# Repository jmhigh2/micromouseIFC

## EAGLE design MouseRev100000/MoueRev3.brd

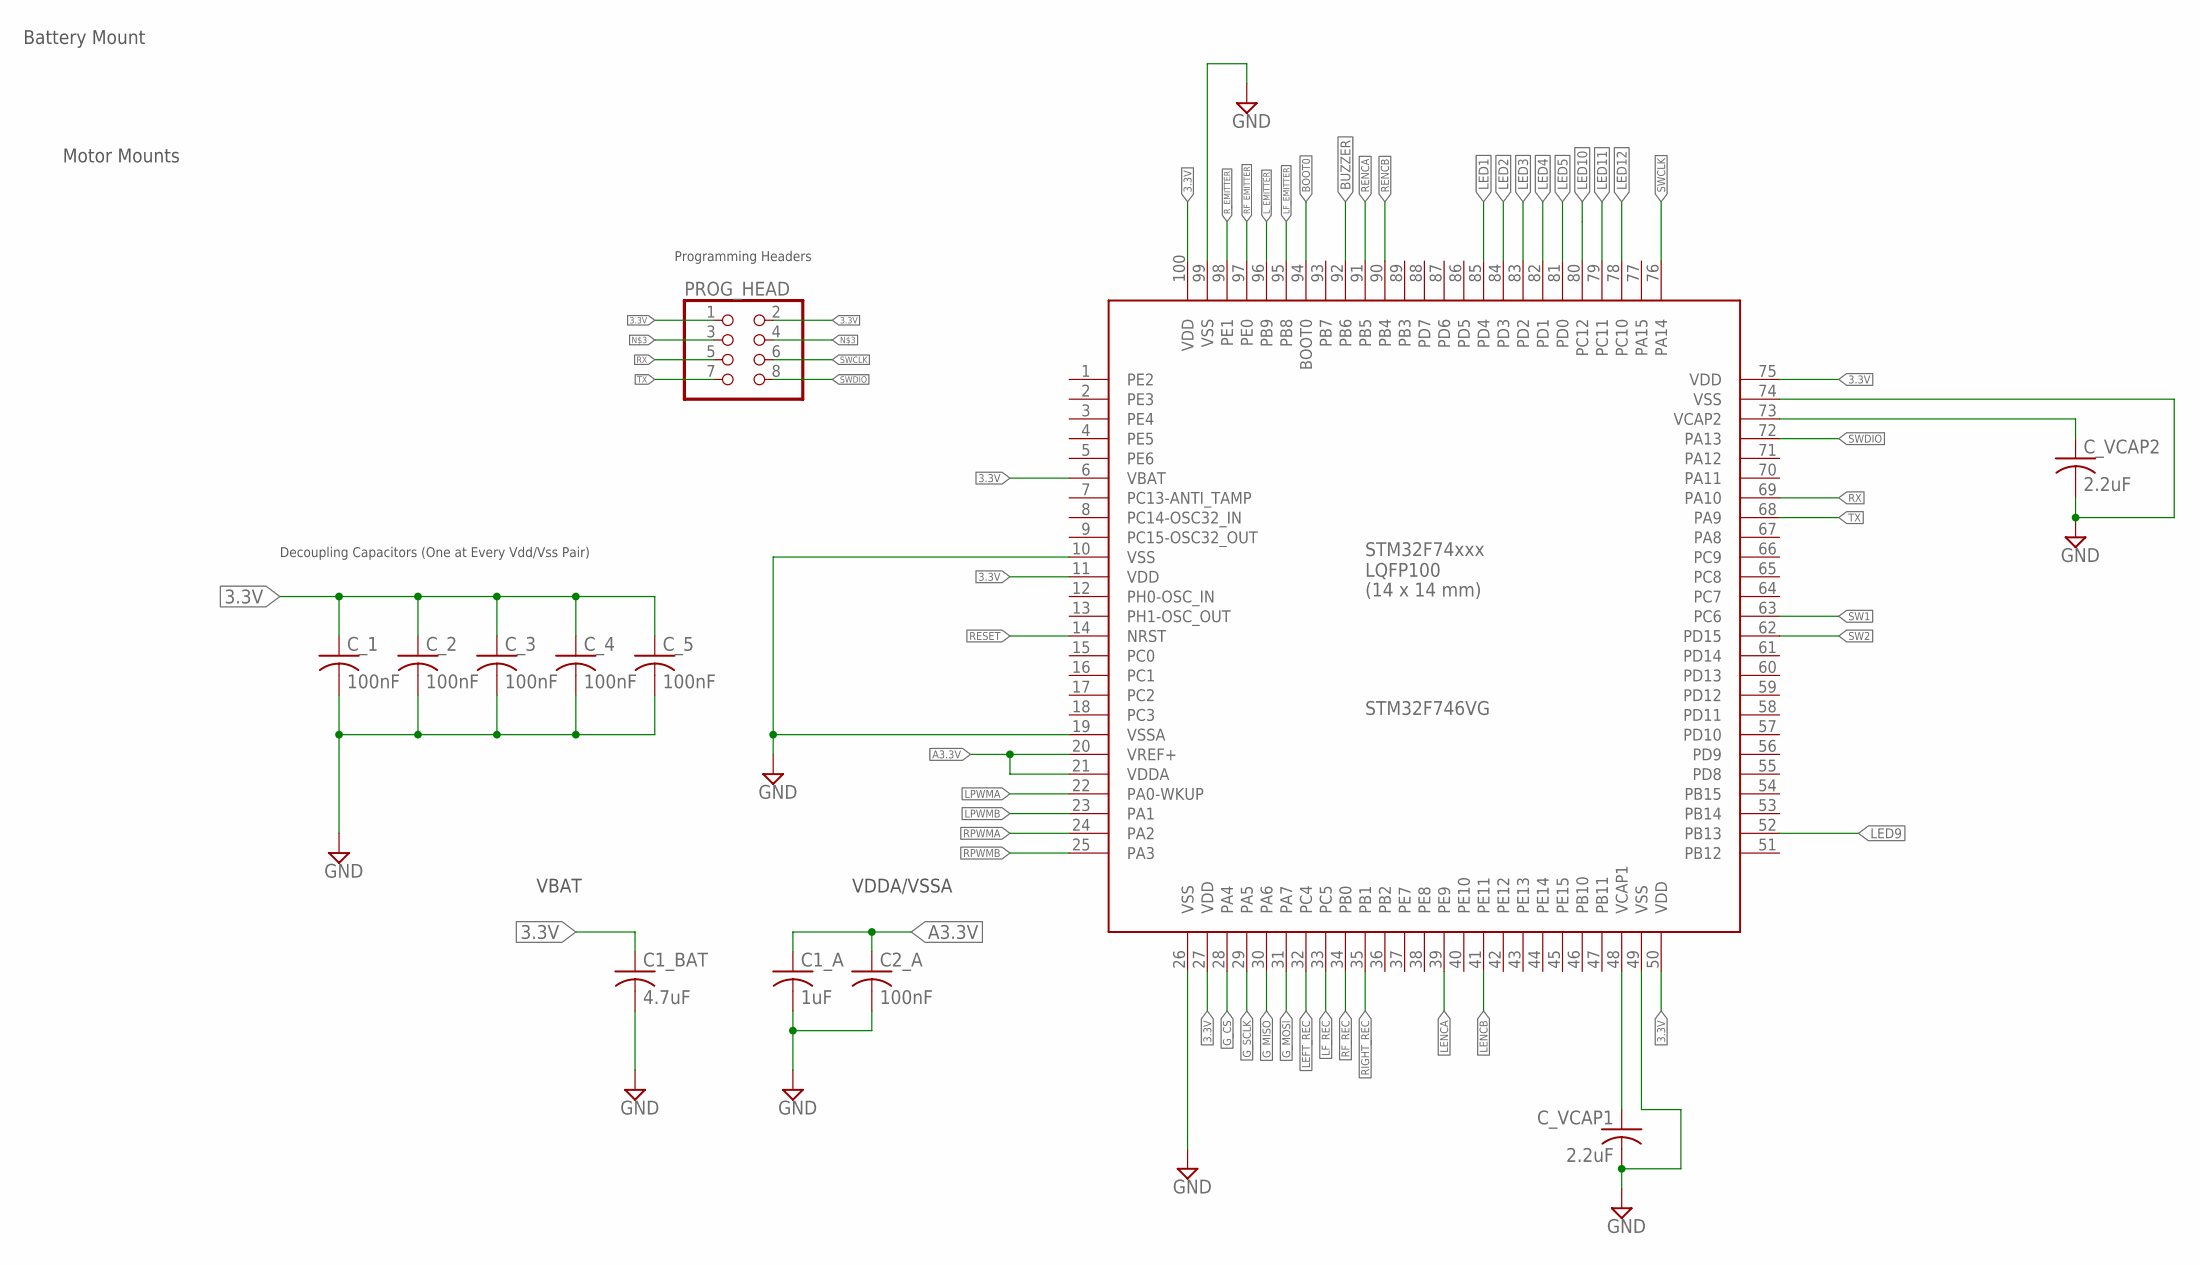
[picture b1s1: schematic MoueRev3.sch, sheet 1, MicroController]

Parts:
C1_A: 1uF; C0603
C1_BAT: 4.7uF; C0603
C2_A: 100nF; C0603
C_1, C_2, C_3, C_4, C_5: 100nF; C0603
C_VCAP1, C_VCAP2: 2.2uF; C0603
PROG_HEAD: PINHD-2X4; 2X04
U$2: MOTOR; MOTOR_MOUNT
U$3: STM32F746VG; LQFP100

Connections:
3.3V: C1_BAT.1, C_1.1, C_2.1, C_3.1, C_4.1, C_5.1, PROG_HEAD.1, PROG_HEAD.2, U$3.6 (VBAT), U$3.11 (VDD), U$3.27 (VDD), U$3.50 (VDD), U$3.75 (VDD), U$3.100 (VDD); also elsewhere on the board
A3.3V: C1_A.1, C2_A.1, U$3.20 (VREF+), U$3.21 (VDDA); also elsewhere on the board
BOOT0: U$3.94 (BOOT0); also elsewhere on the board
BUZZER: U$3.92 (PB6); also elsewhere on the board
G_CS: U$3.28 (PA4); also elsewhere on the board
G_MISO: U$3.30 (PA6); also elsewhere on the board
G_MOSI: U$3.31 (PA7); also elsewhere on the board
G_SCLK: U$3.29 (PA5); also elsewhere on the board
LED1: U$3.85 (PD4); also elsewhere on the board
LED2: U$3.84 (PD3); also elsewhere on the board
LED3: U$3.83 (PD2); also elsewhere on the board
LED4: U$3.82 (PD1); also elsewhere on the board
LED5: U$3.81 (PD0); also elsewhere on the board
LED9: U$3.52 (PB13); also elsewhere on the board
LED10: U$3.80 (PC12); also elsewhere on the board
LED11: U$3.79 (PC11); also elsewhere on the board
LED12: U$3.78 (PC10); also elsewhere on the board
LEFT_REC: U$3.32 (PC4); also elsewhere on the board
LENCA: U$3.39 (PE9); also elsewhere on the board
LENCB: U$3.41 (PE11); also elsewhere on the board
LF_EMITTER: U$3.95 (PB8); also elsewhere on the board
LF_REC: U$3.33 (PC5); also elsewhere on the board
LPWMA: U$3.22 (PA0-WKUP); also elsewhere on the board
LPWMB: U$3.23 (PA1); also elsewhere on the board
L_EMITTER: U$3.96 (PB9); also elsewhere on the board
unnamed 30: C1_A.2, C1_BAT.2, C2_A.2, C_1.2, C_2.2, C_3.2, C_4.2, C_5.2, C_VCAP1.2, C_VCAP2.2, PROG_HEAD.3, PROG_HEAD.4, U$3.10 (VSS), U$3.19 (VSSA), U$3.26 (VSS), U$3.49 (VSS), U$3.74 (VSS), U$3.99 (VSS); also elsewhere on the board
unnamed: C_VCAP2.1, U$3.73 (VCAP2)
unnamed: C_VCAP1.1, U$3.48 (VCAP1)
RENCA: U$3.91 (PB5); also elsewhere on the board
RENCB: U$3.90 (PB4); also elsewhere on the board
RESET: U$3.14 (NRST); also elsewhere on the board
RF_EMITTER: U$3.97 (PE0); also elsewhere on the board
RF_REC: U$3.34 (PB0); also elsewhere on the board
RIGHT_REC: U$3.35 (PB1); also elsewhere on the board
RPWMA: U$3.24 (PA2); also elsewhere on the board
RPWMB: U$3.25 (PA3); also elsewhere on the board
RX: PROG_HEAD.5, U$3.69 (PA10)
R_EMITTER: U$3.98 (PE1); also elsewhere on the board
SW1: U$3.63 (PC6)
SW2: U$3.62 (PD15)
SWCLK: PROG_HEAD.6, U$3.76 (PA14)
SWDIO: PROG_HEAD.8, U$3.72 (PA13)
TX: PROG_HEAD.7, U$3.68 (PA9)

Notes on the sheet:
Decoupling Capacitors (One at Every Vdd/Vss Pair)
Programming Headers
VDDA/VSSA
VBAT
Battery Mount
Motor Mounts

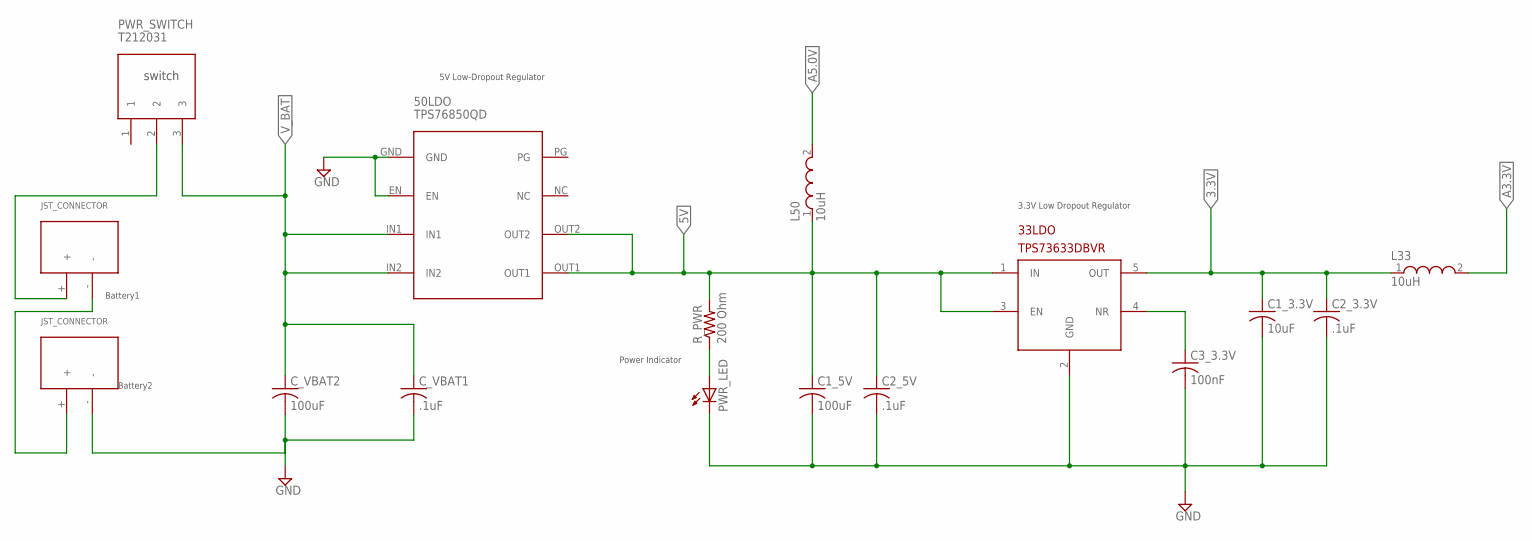
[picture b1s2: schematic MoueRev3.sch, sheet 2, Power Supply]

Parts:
33LDO: TPS73633DBVR; SOT23-DBV
50LDO: TPS76850QD; 8-SOIC(SMT)
C1_3.3V: 10uF; C0603
C1_5V: 100uF; C0603
C2_3.3V, C2_5V: .1uF; C0603
C3_3.3V: 100nF; C0603
C_VBAT1: .1uF; C0603
C_VBAT2: 100uF; C1206
L33, L50: 10uH; WE-MI_0805
PWR_LED: LEDCHIPLED_0805; CHIPLED_0805
PWR_SWITCH: T212031
R_PWR: 200 Ohm; R0603
U$7, U$8: JST_CONNECTOR_FEMALE

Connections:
3.3V: 33LDO.5 (OUT), C1_3.3V.1, C2_3.3V.1, L33.1; also elsewhere on the board
5V: 33LDO.1 (IN), 33LDO.3 (EN), 50LDO.OUT1, 50LDO.OUT2, C1_5V.1, C2_5V.1, L50.1, R_PWR.2; also elsewhere on the board
A3.3V: L33.2; also elsewhere on the board
A5.0V: L50.2; also elsewhere on the board
unnamed: PWR_LED.A, R_PWR.1
unnamed: 33LDO.4 (NR), C3_3.3V.1
unnamed 30: 33LDO.2 (GND), 50LDO.EN, 50LDO.GND, C1_3.3V.2, C1_5V.2, C2_3.3V.2, C2_5V.2, C3_3.3V.2, C_VBAT1.2, C_VBAT2.2, PWR_LED.C, U$8.-; also elsewhere on the board
unnamed: U$7.-, U$8.+
unnamed: PWR_SWITCH.2, U$7.+
V_BAT: 50LDO.IN1, 50LDO.IN2, C_VBAT1.1, C_VBAT2.1, PWR_SWITCH.3; also elsewhere on the board

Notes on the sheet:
Battery1
Battery2
5V Low-Dropout Regulator
3.3V Low Dropout Regulator
Power Indicator
switch

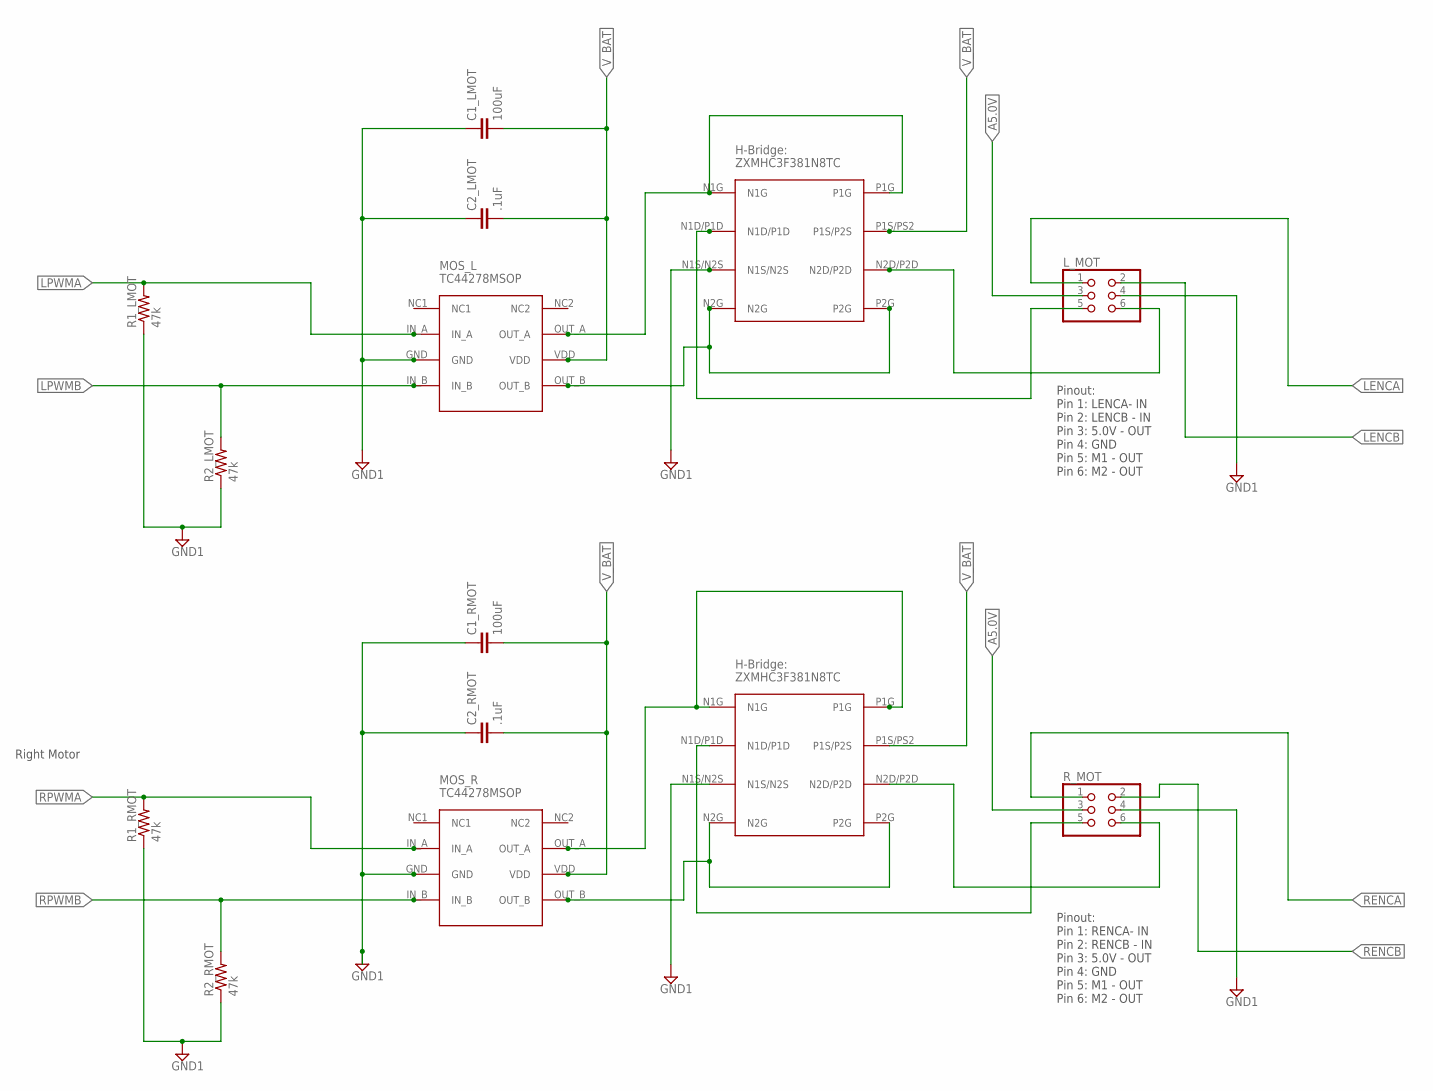
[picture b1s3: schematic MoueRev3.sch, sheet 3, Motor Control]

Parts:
C1_LMOT, C1_RMOT: 100uF; C1206
C2_LMOT, C2_RMOT: .1uF; C0805
HB_L: ZXMHC3F381N8TC; 8-SOIC
HB_R: ZXMHC3F381N8TC; 8-SOIC
L_MOT: PINHD-2X3; 2X03
MOS_L: TC44278MSOP
MOS_R: TC44278MSOP
R1_LMOT, R1_RMOT, R2_LMOT, R2_RMOT: 47k; R0603
R_MOT: PINHD-2X3; 2X03

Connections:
A5.0V: L_MOT.3, R_MOT.3; also elsewhere on the board
LENCA: L_MOT.1; also elsewhere on the board
LENCB: L_MOT.2; also elsewhere on the board
LPWMA: MOS_L.IN_A, R1_LMOT.2; also elsewhere on the board
LPWMB: MOS_L.IN_B, R2_LMOT.2; also elsewhere on the board
unnamed 30: C1_LMOT.1, C1_RMOT.1, C2_LMOT.1, C2_RMOT.1, HB_L.N1S/N2S, HB_R.N1S/N2S, L_MOT.4, MOS_L.GND, MOS_R.GND, R1_LMOT.1, R1_RMOT.1, R2_LMOT.1, R2_RMOT.1, R_MOT.4; also elsewhere on the board
unnamed: HB_L.N1G, HB_L.P1G, MOS_L.OUT_A
unnamed: HB_L.N2G, HB_L.P2G, MOS_L.OUT_B
unnamed: HB_R.N1G, HB_R.P1G, MOS_R.OUT_A
unnamed: HB_L.N1D/P1D, L_MOT.5
unnamed: HB_L.N2D/P2D, L_MOT.6
unnamed: HB_R.N2G, HB_R.P2G, MOS_R.OUT_B
unnamed: HB_R.N1D/P1D, R_MOT.5
unnamed: HB_R.N2D/P2D, R_MOT.6
RENCA: R_MOT.1; also elsewhere on the board
RENCB: R_MOT.2; also elsewhere on the board
RPWMA: MOS_R.IN_A, R1_RMOT.2; also elsewhere on the board
RPWMB: MOS_R.IN_B, R2_RMOT.2; also elsewhere on the board
V_BAT: C1_LMOT.2, C1_RMOT.2, C2_LMOT.2, C2_RMOT.2, HB_L.P1S/PS2 (P1S/P2S), HB_R.P1S/PS2 (P1S/P2S), MOS_L.VDD, MOS_R.VDD; also elsewhere on the board

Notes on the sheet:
Pinout: Pin 1: LENCA- IN Pin 2: LENCB - IN Pin 3: 5.0V - OUT Pin 4: GND Pin 5: M1 - OUT Pin 6: M2 - OUT
Right Motor
Pinout: Pin 1: RENCA- IN Pin 2: RENCB - IN Pin 3: 5.0V - OUT Pin 4: GND Pin 5: M1 - OUT Pin 6: M2 - OUT

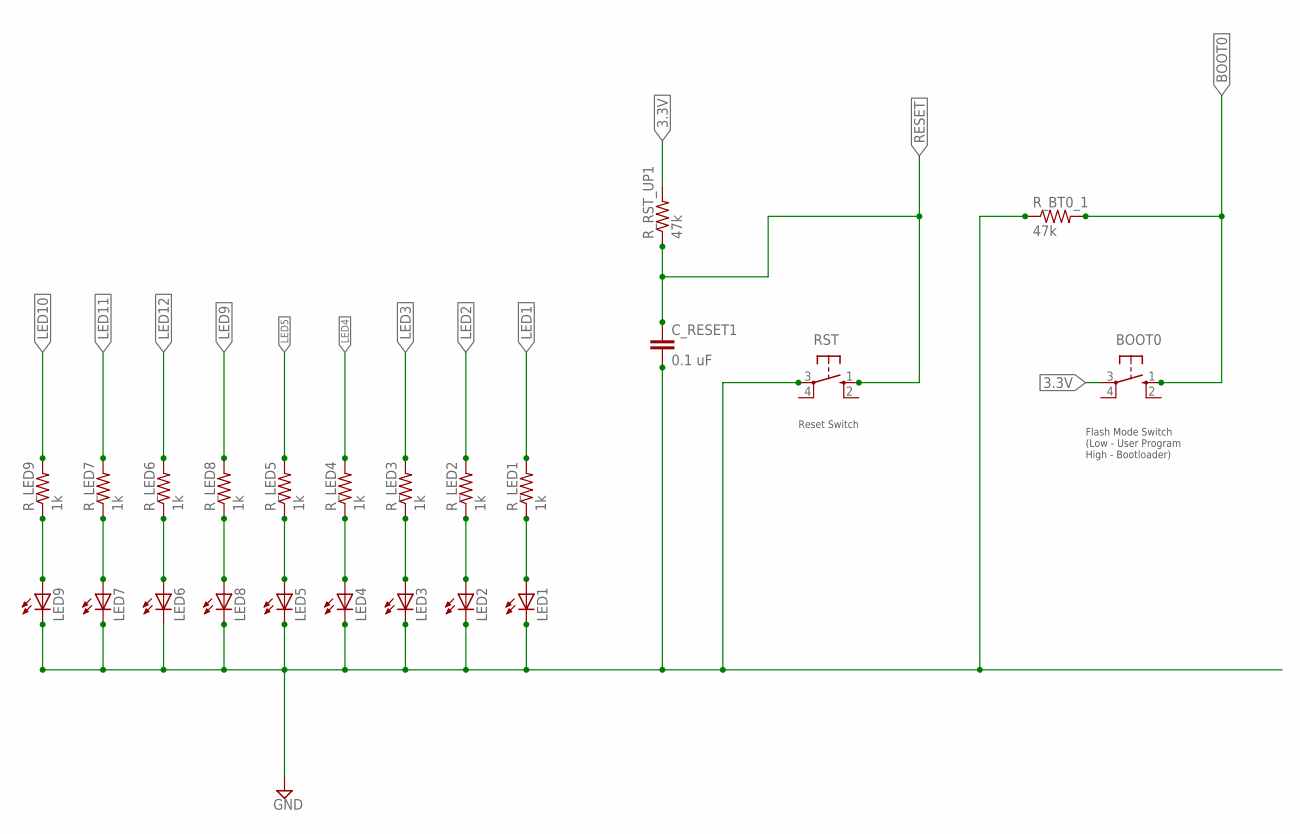
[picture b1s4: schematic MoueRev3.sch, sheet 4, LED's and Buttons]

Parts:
BOOT0: 10-XX; B3F-10XX
C_RESET1: 0.1 uF; C0603
LED1, LED2, LED3, LED4, LED5, LED6, LED7, LED8, LED9: LEDCHIPLED_0805; CHIPLED_0805
RST: 10-XX; B3F-10XX
R_BT0_1: 47k; R0603
R_LED1, R_LED2, R_LED3, R_LED4, R_LED5, R_LED6, R_LED7, R_LED8, R_LED9: 1k; R0603
R_RST_UP1: 47k; R0603

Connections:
3.3V: BOOT0.3, R_RST_UP1.2; also elsewhere on the board
BOOT0: BOOT0.1 (S), R_BT0_1.2; also elsewhere on the board
GND: C_RESET1.2, LED1.C, LED2.C, LED3.C, LED4.C, LED5.C, LED6.C, LED7.C, LED8.C, LED9.C, RST.3, R_BT0_1.1
LED1: R_LED1.2; also elsewhere on the board
LED2: R_LED2.2; also elsewhere on the board
LED3: R_LED3.2; also elsewhere on the board
LED4: R_LED4.2; also elsewhere on the board
LED5: R_LED5.2; also elsewhere on the board
LED9: R_LED8.2; also elsewhere on the board
LED10: R_LED9.2; also elsewhere on the board
LED11: R_LED7.2; also elsewhere on the board
LED12: R_LED6.2; also elsewhere on the board
unnamed: LED8.A, R_LED8.1
unnamed: LED6.A, R_LED6.1
unnamed: LED7.A, R_LED7.1
unnamed: LED9.A, R_LED9.1
unnamed: LED1.A, R_LED1.1
unnamed: LED2.A, R_LED2.1
unnamed: LED3.A, R_LED3.1
unnamed: LED4.A, R_LED4.1
unnamed: LED5.A, R_LED5.1
RESET: C_RESET1.1, RST.1 (S), R_RST_UP1.1; also elsewhere on the board

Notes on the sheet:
Reset Switch
Flash Mode Switch (Low - User Program High - Bootloader)

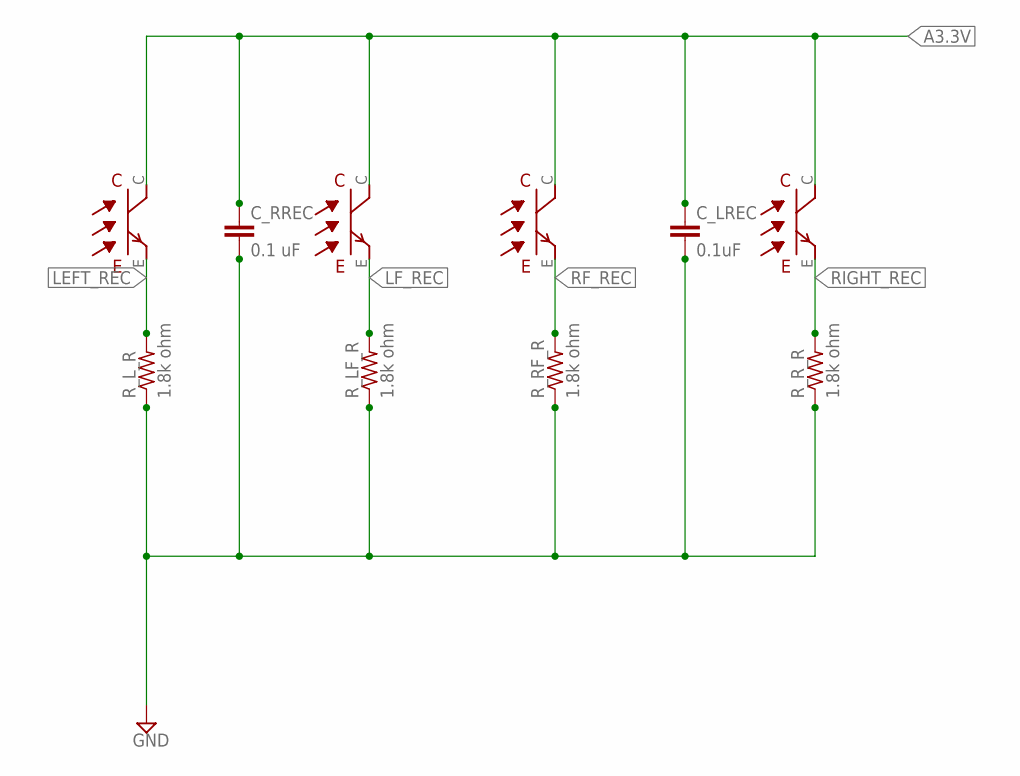
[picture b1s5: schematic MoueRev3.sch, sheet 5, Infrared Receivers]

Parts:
C_LREC: 0.1uF; C0603
C_RREC: 0.1 uF; C0603
LF_REC: RECEIVER
L_REC: RECEIVER
RF_REC: RECEIVER
R_LF_R: 1.8k ohm; R0603
R_L_R: 1.8k ohm; R0603
R_REC: RECEIVER
R_RF_R: 1.8k ohm; R0603
R_R_R: 1.8k ohm; R0603

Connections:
A3.3V: C_LREC.1, C_RREC.1, LF_REC.C, L_REC.C, RF_REC.C, R_REC.C; also elsewhere on the board
LEFT_REC: L_REC.E, R_L_R.2; also elsewhere on the board
LF_REC: LF_REC.E, R_LF_R.2; also elsewhere on the board
unnamed 30: C_LREC.2, C_RREC.2, R_LF_R.1, R_L_R.1, R_RF_R.1, R_R_R.1; also elsewhere on the board
RF_REC: RF_REC.E, R_RF_R.2; also elsewhere on the board
RIGHT_REC: R_REC.E, R_R_R.2; also elsewhere on the board

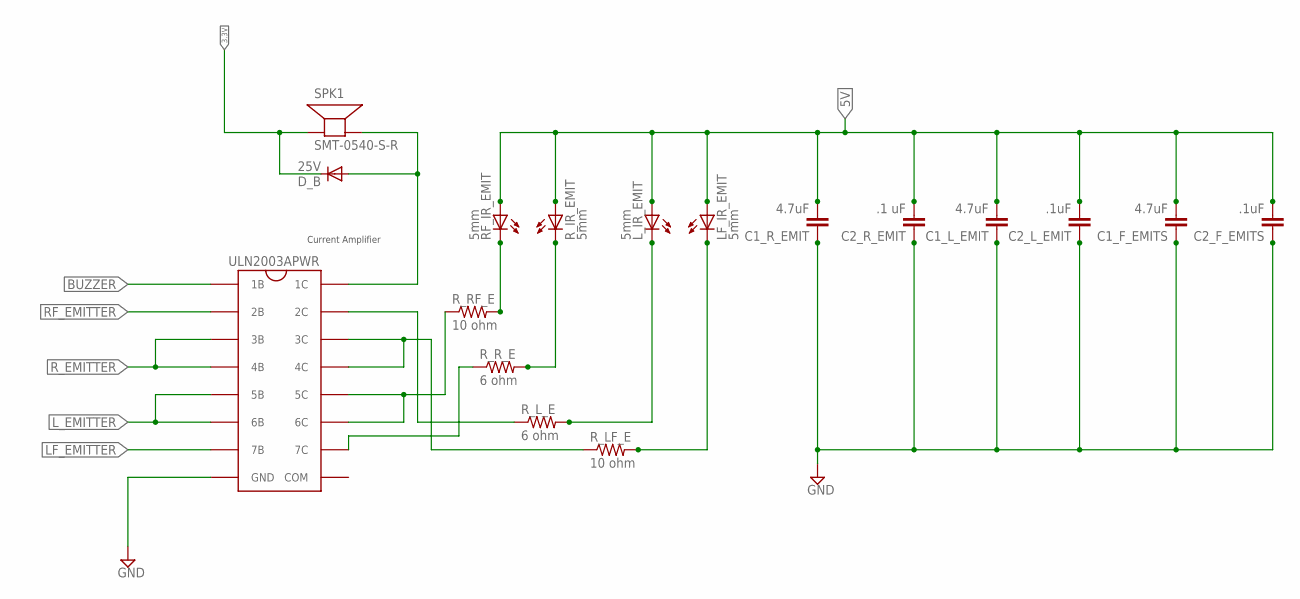
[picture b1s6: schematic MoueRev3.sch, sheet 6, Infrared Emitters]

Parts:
C1_F_EMITS, C1_L_EMIT, C1_R_EMIT: 4.7uF; C0603
C2_F_EMITS, C2_L_EMIT: .1uF; C0603
C2_R_EMIT: .1 uF; C0603
D_B: 25V; SOD123
LF_IR_EMIT: 5mm; LED5MM
L_IR_EMIT: 5mm; LED5MM
RF_IR_EMIT: 5mm; LED5MM
R_IR_EMIT: 5mm; LED5MM
R_LF_E: 10 ohm; R0603
R_L_E: 6 ohm; R0603
R_RF_E: 10 ohm; R0603
R_R_E: 6 ohm; R0603
SPK1: SMT-0540-S-R
U$9: ULN2003APWR

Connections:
3.3V: D_B.C, SPK1.- (+); also elsewhere on the board
5V: C1_F_EMITS.2, C1_L_EMIT.2, C1_R_EMIT.2, C2_F_EMITS.2, C2_L_EMIT.2, C2_R_EMIT.2, LF_IR_EMIT.A, L_IR_EMIT.A, RF_IR_EMIT.A, R_IR_EMIT.A; also elsewhere on the board
BUZZER: U$9.1B; also elsewhere on the board
LF_EMITTER: U$9.7B; also elsewhere on the board
L_EMITTER: U$9.5B, U$9.6B; also elsewhere on the board
unnamed 30: C1_F_EMITS.1, C1_L_EMIT.1, C1_R_EMIT.1, C2_F_EMITS.1, C2_L_EMIT.1, C2_R_EMIT.1, U$9.GND; also elsewhere on the board
unnamed: R_L_E.1, U$9.2C
unnamed: R_R_E.1, U$9.7C
unnamed: RF_IR_EMIT.K (C), R_RF_E.2
unnamed: R_LF_E.1, U$9.3C, U$9.4C
unnamed: R_IR_EMIT.K (C), R_R_E.2
unnamed: L_IR_EMIT.K (C), R_L_E.2
unnamed: R_RF_E.1, U$9.5C, U$9.6C
unnamed: LF_IR_EMIT.K (C), R_LF_E.2
unnamed: D_B.A, SPK1.+ (-), U$9.1C
RF_EMITTER: U$9.2B; also elsewhere on the board
R_EMITTER: U$9.3B, U$9.4B; also elsewhere on the board

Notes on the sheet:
Current Amplifier

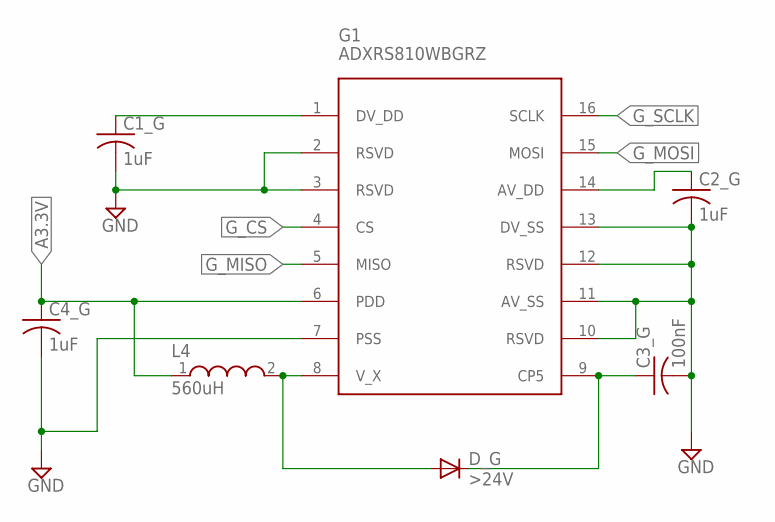
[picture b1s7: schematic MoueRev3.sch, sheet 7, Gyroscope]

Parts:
C1_G, C2_G, C4_G: 1uF; C0603
C3_G: 100nF; C0603
D_G: >24V; SOD123
G1: ADXRS810; SOIC-16
L4: 560uH; WE-MI_1206

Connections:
A3.3V: C4_G.1, G1.6 (PDD), L4.1; also elsewhere on the board
G_CS: G1.4 (CS); also elsewhere on the board
G_MISO: G1.5 (MISO); also elsewhere on the board
G_MOSI: G1.15 (MOSI); also elsewhere on the board
G_SCLK: G1.16 (SCLK); also elsewhere on the board
unnamed 30: C1_G.2, C2_G.2, C3_G.2, C4_G.2, G1.2 (RSVD), G1.3 (RSVD), G1.7 (PSS), G1.10 (RSVD), G1.11 (AV_SS), G1.12 (RSVD), G1.13 (DV_SS); also elsewhere on the board
unnamed: C1_G.1, G1.1 (DV_DD)
unnamed: D_G.A, G1.8 (V_X), L4.2
unnamed: C3_G.1, D_G.C, G1.9 (CP5)
unnamed: C2_G.1, G1.14 (AV_DD)

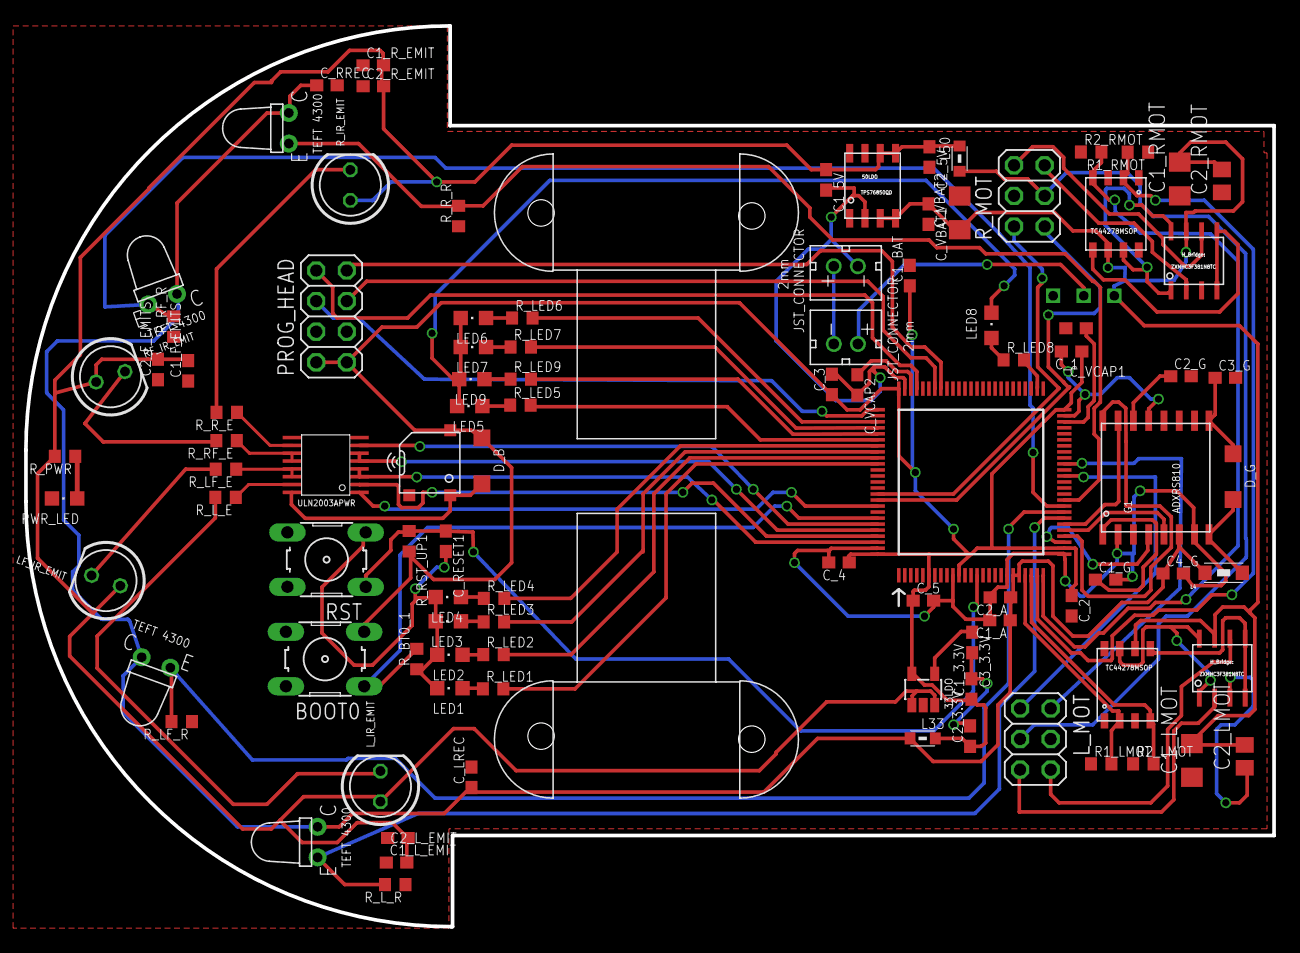
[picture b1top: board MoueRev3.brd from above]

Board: 2 copper layers, 103.7 x 74.8 mm, 101 parts (0 on the bottom side), 79 nets.

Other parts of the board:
U$1: MOTOR; MOTOR_MOUNT

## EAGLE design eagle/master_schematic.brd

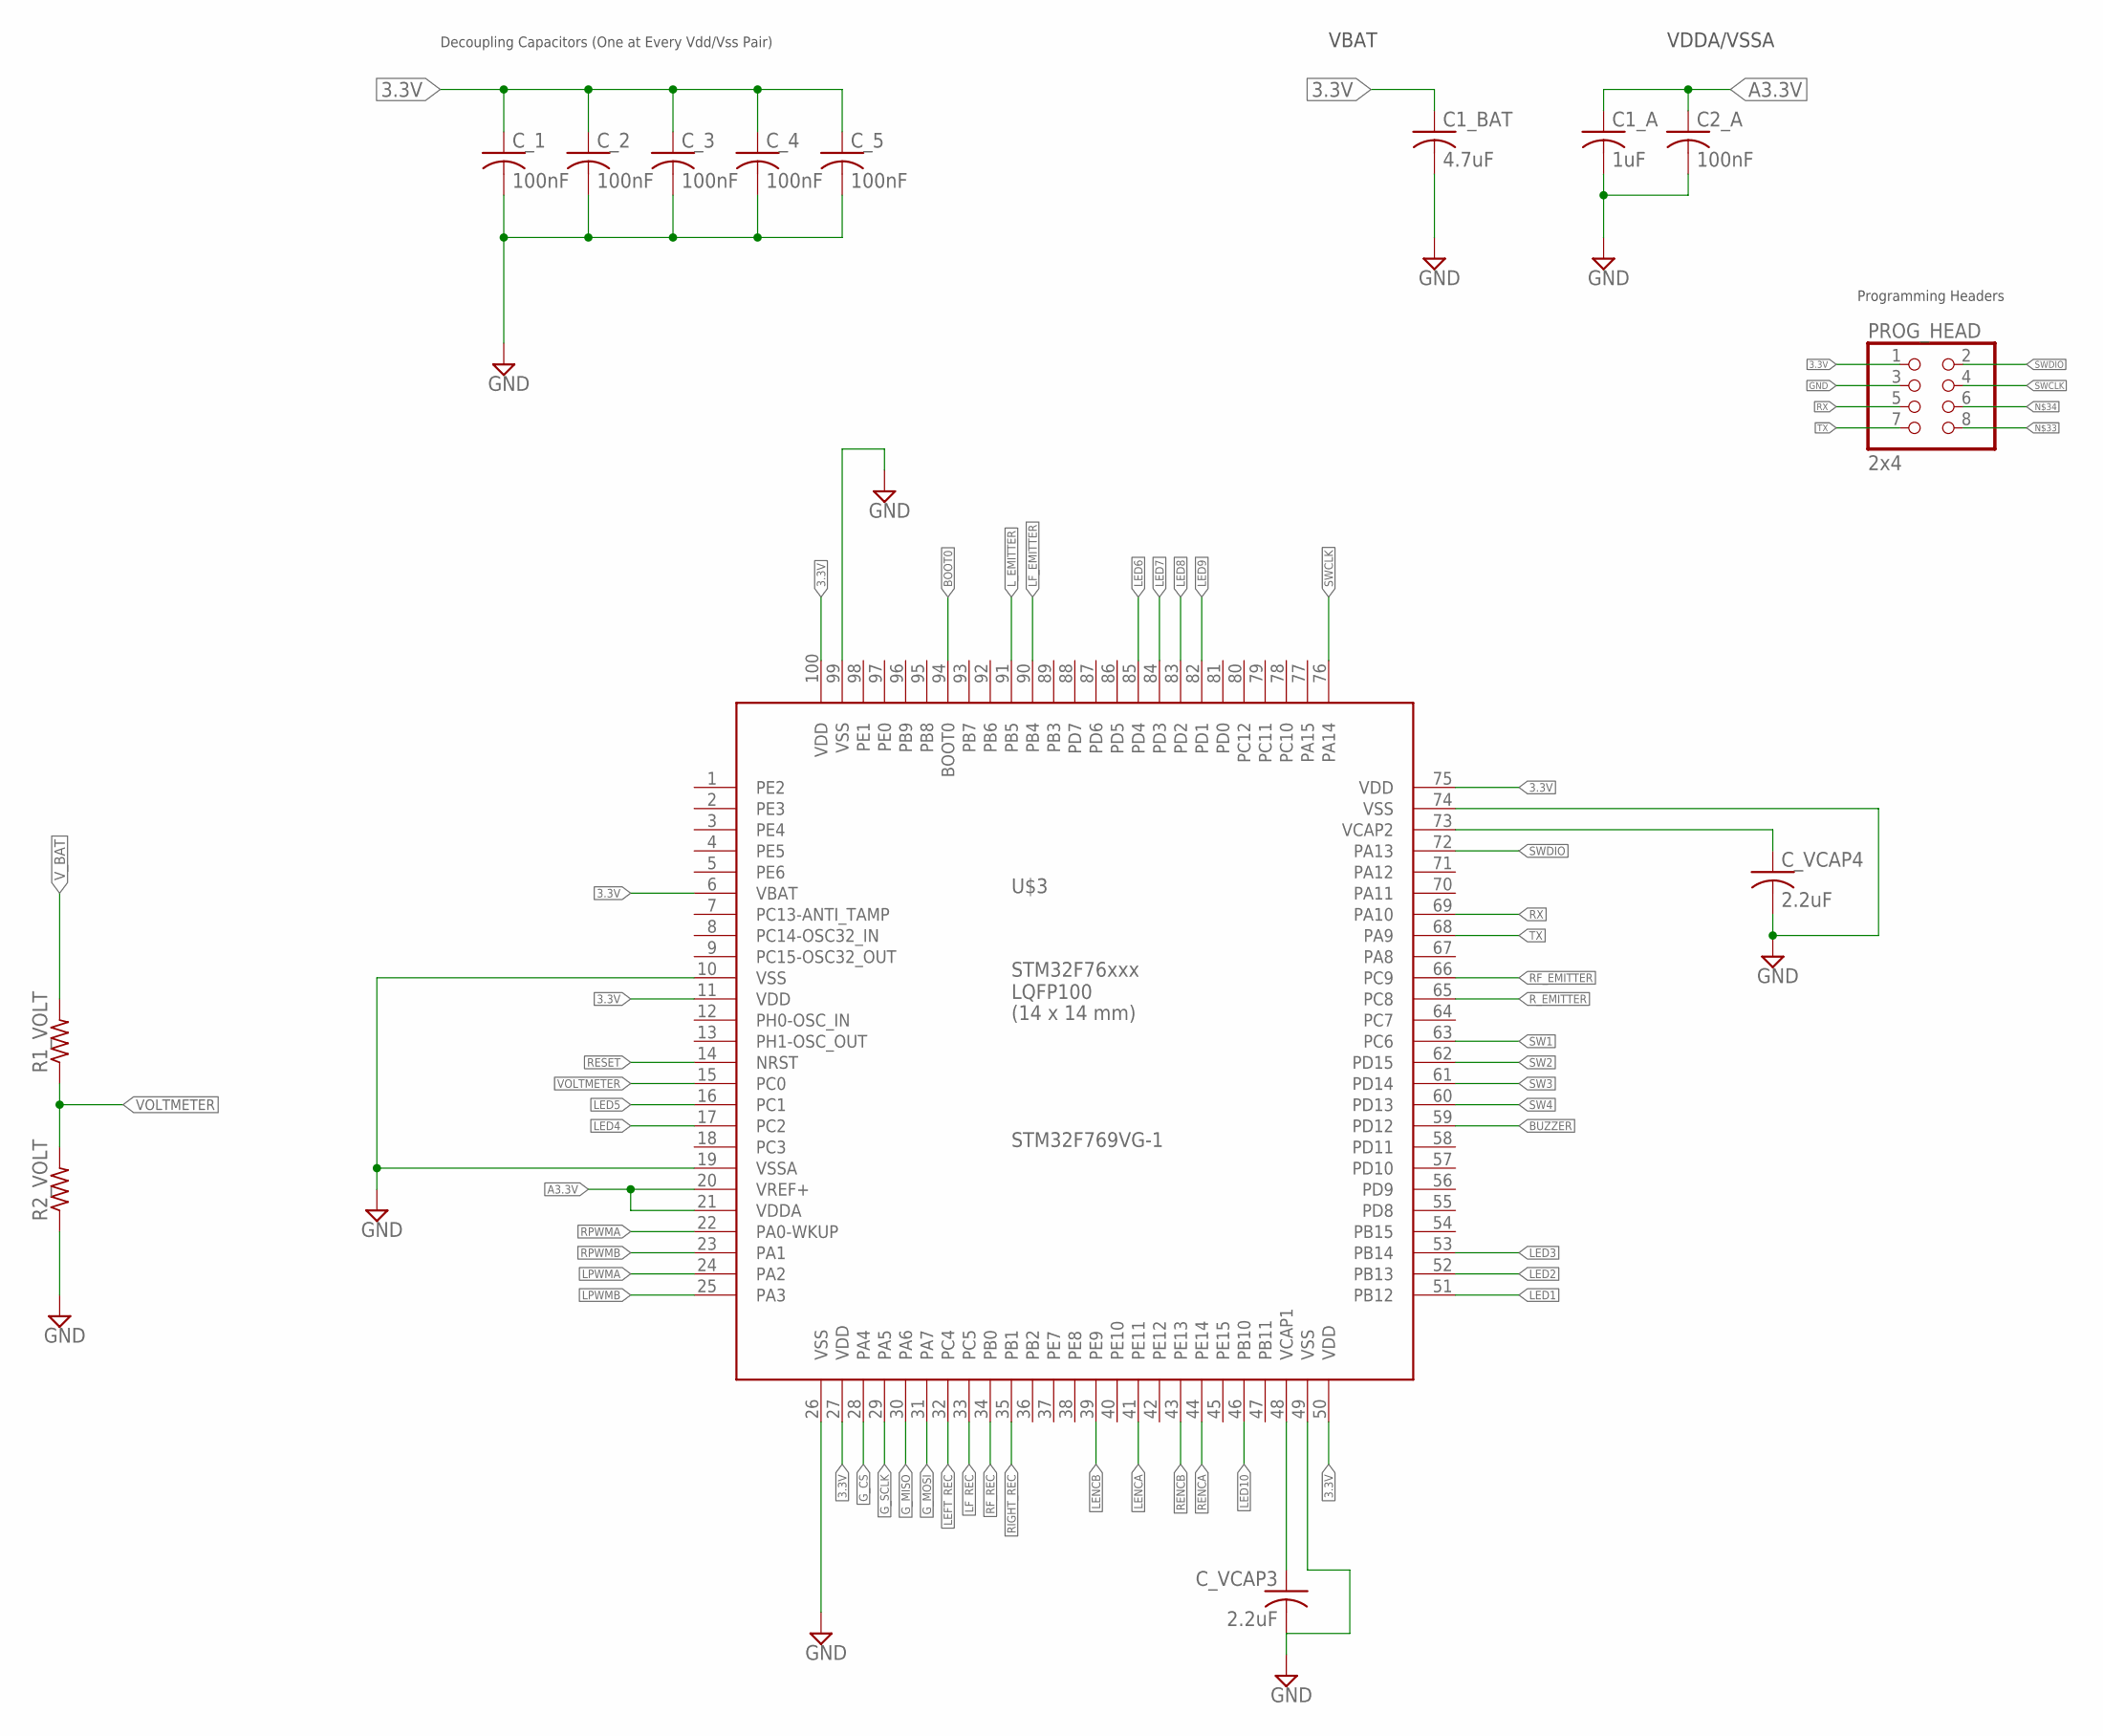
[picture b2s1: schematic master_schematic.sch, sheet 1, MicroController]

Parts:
C1_A: 1uF; C0603
C1_BAT: 4.7uF; C0603
C2_A: 100nF; C0603
C_1, C_2, C_3, C_4, C_5: 100nF; C0603
C_VCAP3, C_VCAP4: 2.2uF; C0603
PROG_HEAD: 2x4; 2X04
R1_VOLT, R2_VOLT: R-US_R0805; R0805
U$3: STM32F769VG-1; LQFP100

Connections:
3.3V: C1_BAT.1, C_1.1, C_2.1, C_3.1, C_4.1, C_5.1, PROG_HEAD.1, U$3.6 (VBAT), U$3.11 (VDD), U$3.27 (VDD), U$3.50 (VDD), U$3.75 (VDD), U$3.100 (VDD); also elsewhere on the board
A3.3V: C1_A.1, C2_A.1, U$3.20 (VREF+), U$3.21 (VDDA); also elsewhere on the board
BOOT0: U$3.94 (BOOT0); also elsewhere on the board
BUZZER: U$3.59 (PD12); also elsewhere on the board
GND: C1_A.2, C1_BAT.2, C2_A.2, C_1.2, C_2.2, C_3.2, C_4.2, C_5.2, C_VCAP3.2, C_VCAP4.2, PROG_HEAD.3, R2_VOLT.1, U$3.10 (VSS), U$3.19 (VSSA), U$3.26 (VSS), U$3.49 (VSS), U$3.74 (VSS), U$3.99 (VSS); also elsewhere on the board
G_CS: U$3.28 (PA4); also elsewhere on the board
G_MISO: U$3.30 (PA6); also elsewhere on the board
G_MOSI: U$3.31 (PA7); also elsewhere on the board
G_SCLK: U$3.29 (PA5); also elsewhere on the board
LED1: U$3.51 (PB12); also elsewhere on the board
LED2: U$3.52 (PB13); also elsewhere on the board
LED3: U$3.53 (PB14); also elsewhere on the board
LED4: U$3.17 (PC2); also elsewhere on the board
LED5: U$3.16 (PC1); also elsewhere on the board
LED6: U$3.85 (PD4); also elsewhere on the board
LED7: U$3.84 (PD3); also elsewhere on the board
LED8: U$3.83 (PD2); also elsewhere on the board
LED9: U$3.82 (PD1); also elsewhere on the board
LED10: U$3.46 (PB10)
LEFT_REC: U$3.32 (PC4); also elsewhere on the board
LF_EMITTER: U$3.90 (PB4); also elsewhere on the board
LF_REC: U$3.33 (PC5); also elsewhere on the board
LPWMA: U$3.24 (PA2); also elsewhere on the board
LPWMB: U$3.25 (PA3); also elsewhere on the board
L_EMITTER: U$3.91 (PB5); also elsewhere on the board
L_ENC_A: U$3.41 (PE11); also elsewhere on the board
L_ENC_B: U$3.39 (PE9); also elsewhere on the board
unnamed: C_VCAP4.1, U$3.73 (VCAP2)
unnamed: C_VCAP3.1, U$3.48 (VCAP1)
RESET: U$3.14 (NRST); also elsewhere on the board
RF_EMITTER: U$3.66 (PC9); also elsewhere on the board
RF_REC: U$3.34 (PB0); also elsewhere on the board
RIGHT_REC: U$3.35 (PB1); also elsewhere on the board
RPWMA: U$3.22 (PA0-WKUP); also elsewhere on the board
RPWMB: U$3.23 (PA1); also elsewhere on the board
RX: PROG_HEAD.5, U$3.69 (PA10)
R_EMITTER: U$3.65 (PC8); also elsewhere on the board
R_ENC_A: U$3.44 (PE14); also elsewhere on the board
R_ENC_B: U$3.43 (PE13); also elsewhere on the board
SW1: U$3.63 (PC6)
SW2: U$3.62 (PD15)
SW3: U$3.61 (PD14)
SW4: U$3.60 (PD13)
SWCLK: PROG_HEAD.4, U$3.76 (PA14)
SWDIO: PROG_HEAD.2, U$3.72 (PA13)
TX: PROG_HEAD.7, U$3.68 (PA9)
VOLTMETER: R1_VOLT.1, R2_VOLT.2, U$3.15 (PC0)

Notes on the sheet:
Decoupling Capacitors (One at Every Vdd/Vss Pair)
Programming Headers
VDDA/VSSA
VBAT

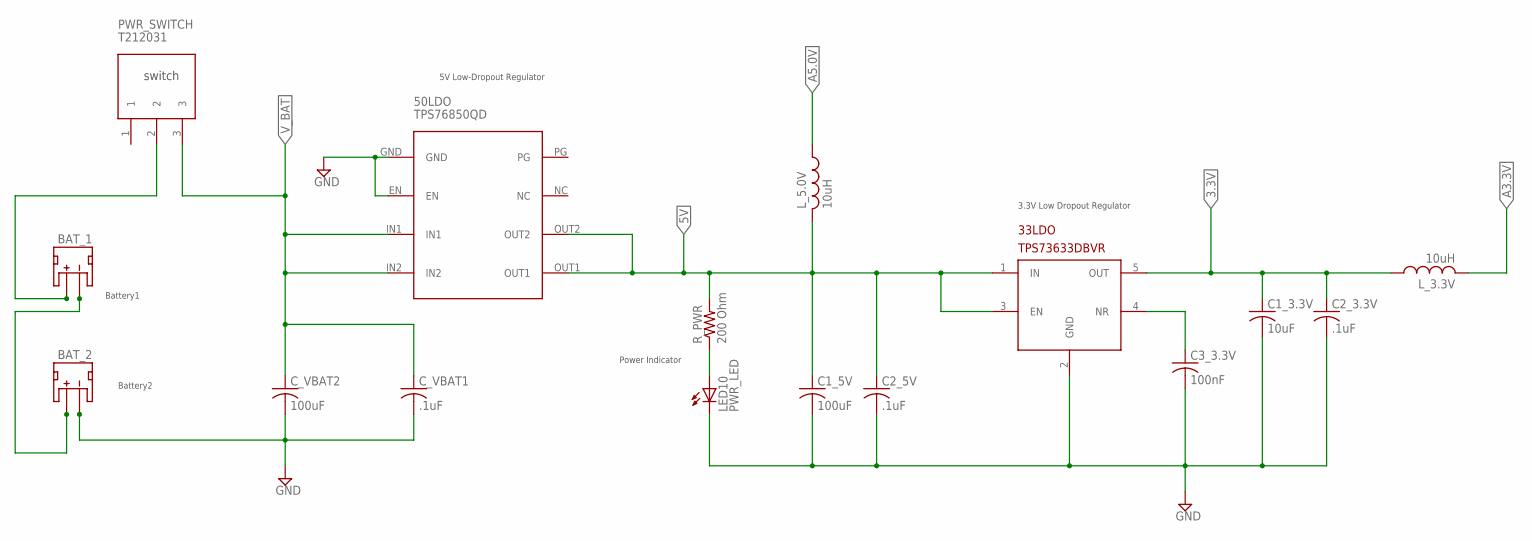
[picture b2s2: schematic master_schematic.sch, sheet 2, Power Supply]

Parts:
33LDO: TPS73633DBVR; SOT23-DBV
50LDO: TPS76850QD; 8-SOIC(SMT)
BAT_1, BAT_2: JST_2mm; JST-2-SMD
C1_3.3V: 10uF; C0603
C1_5V: 100uF; C0603
C2_3.3V, C2_5V: .1uF; C0603
C3_3.3V: 100nF; C0603
C_VBAT1: .1uF; C0603
C_VBAT2: 100uF; C0603
LED10: PWR_LED; CHIPLED_0805
L_3.3V, L_5.0V: 10uH; L1812
PWR_SWITCH: T212031
R_PWR: 200 Ohm; M0805

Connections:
3.3V: 33LDO.5 (OUT), C1_3.3V.1, C2_3.3V.1, L_3.3V.1; also elsewhere on the board
5V: 33LDO.1 (IN), 33LDO.3 (EN), 50LDO.OUT1, 50LDO.OUT2, C1_5V.1, C2_5V.1, L_5.0V.2, R_PWR.2; also elsewhere on the board
A3.3V: L_3.3V.2; also elsewhere on the board
A5.0V: L_5.0V.1; also elsewhere on the board
GND: 33LDO.2 (GND), 50LDO.EN, 50LDO.GND, BAT_2.1 (-), C1_3.3V.2, C1_5V.2, C2_3.3V.2, C2_5V.2, C3_3.3V.2, C_VBAT1.2, C_VBAT2.2, LED10.C; also elsewhere on the board
unnamed: LED10.A, R_PWR.1
unnamed: 33LDO.4 (NR), C3_3.3V.1
unnamed: BAT_1.1 (-), BAT_2.2 (+)
unnamed 54: BAT_1.2 (+), PWR_SWITCH.2; also elsewhere on the board
V_BAT: 50LDO.IN1, 50LDO.IN2, C_VBAT1.1, C_VBAT2.1, PWR_SWITCH.3; also elsewhere on the board

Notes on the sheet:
Battery1
Battery2
5V Low-Dropout Regulator
3.3V Low Dropout Regulator
Power Indicator
switch

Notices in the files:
parts and their libraries:
EagleLibrary_Wuerth_Elektronik_eiSos_rev: Copyright: Würth Elektronik
SparkFun-Connectors: Licensing: Creative Commons ShareAlike 4.0 International - https://creativecommons.org/licenses/by-sa/4.0
